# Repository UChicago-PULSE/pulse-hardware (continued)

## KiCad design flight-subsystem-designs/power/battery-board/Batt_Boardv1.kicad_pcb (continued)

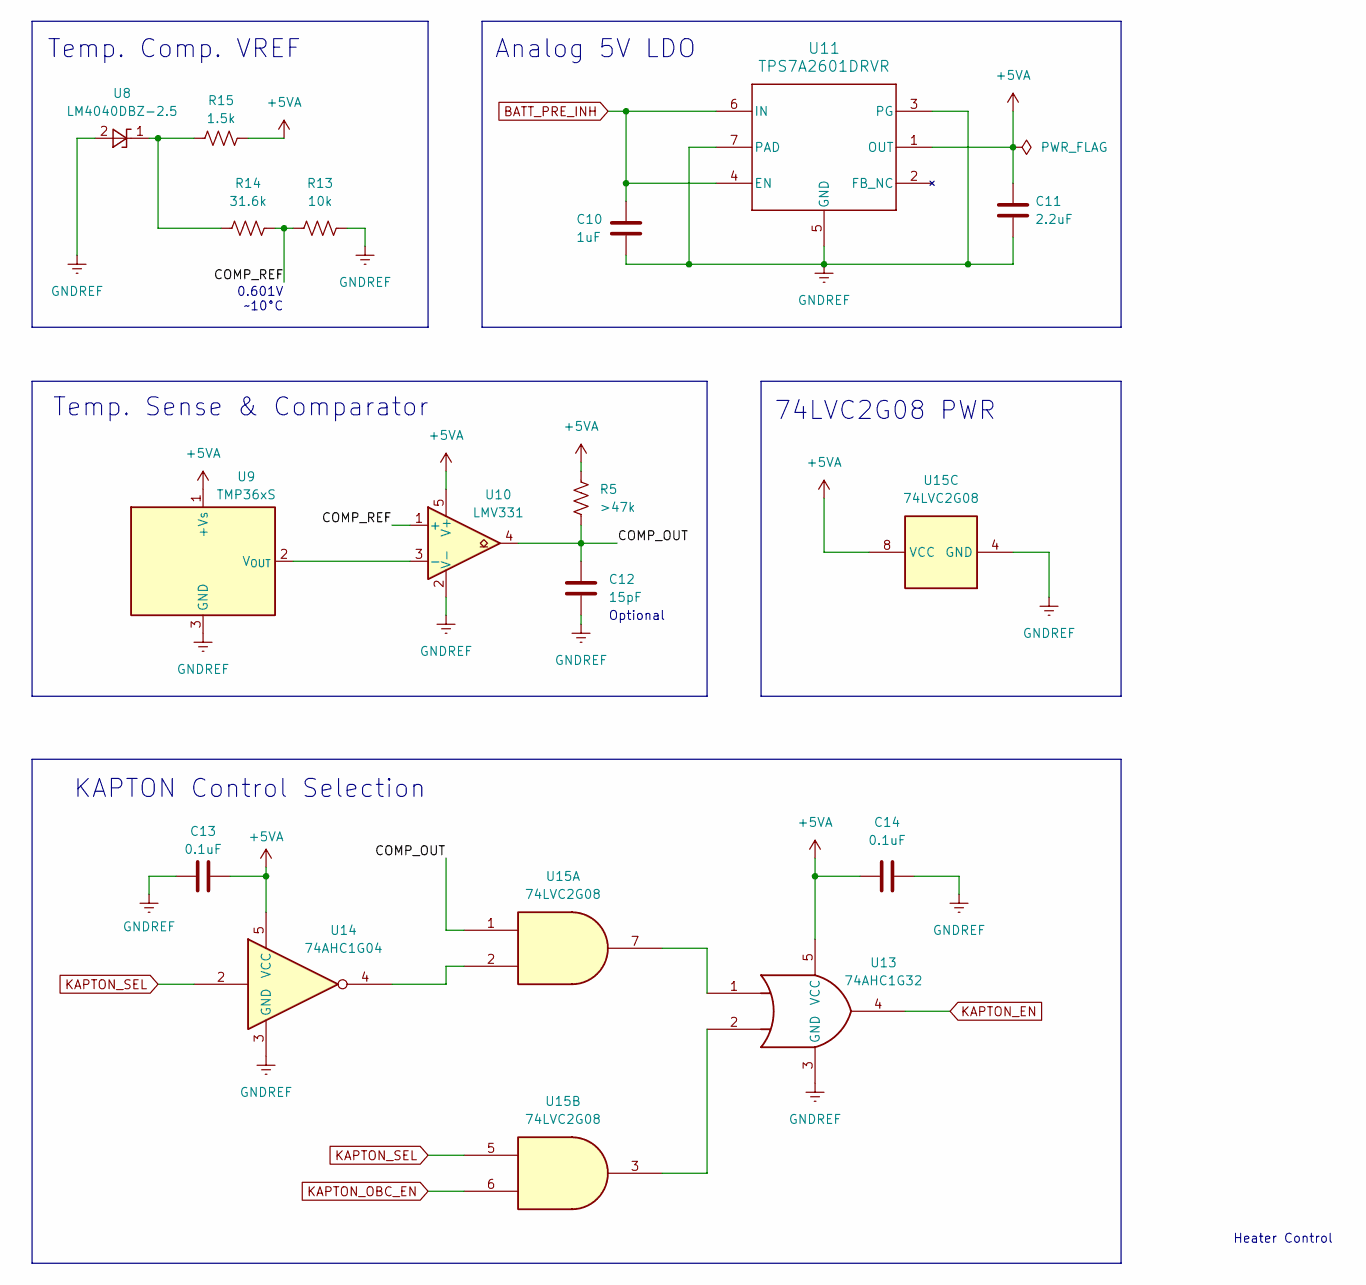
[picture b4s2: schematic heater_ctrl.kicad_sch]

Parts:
C10: 1uF; C_0805_2012Metric
C11: 2.2uF; C_0805_2012Metric
C12: 15pF; C_0805_2012Metric
C13, C14: 0.1uF; C_0805_2012Metric
R5: >47k; R_0805_2012Metric
R13: 10k; R_0805_2012Metric
R14: 31.6k; R_0805_2012Metric
R15: 1.5k; R_0805_2012Metric
U8: LM4040DBZ-2.5; SOT-23
U9: TMP36xS; TO-92_Inline
U10: LMV331; SOT-23-5
U11: TPS7A2601DRVR; DRV0006A_NV
U13: 74AHC1G32; SOT-23-5
U14: 74AHC1G04; SOT-23-5
U15: 74LVC2G08; VSSOP-8_2.3x2mm_P0.5mm

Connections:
+5VA: C11.1, C13.2, C14.1, R5.1, R15.2, U9.1 (+Vs), U10.5 (V+), U11.1 (OUT), U13.5 (VCC), U14.5 (VCC), U15.8 (VCC); also elsewhere on the board
/Heater Control/COMP_OUT: C12.1, R5.2, U10.4, U15.1
/Heater Control/COMP_REF: R13.1, R14.2, U10.1 (+)
BATT_PRE_INH: C10.1, U11.4 (EN), U11.6 (IN); also elsewhere on the board
GNDREF: C10.2, C11.2, C12.2, C13.1, C14.2, R13.2, U8.2 (A), U9.3 (GND), U10.2 (V-), U11.3 (PG), U11.5 (GND), U11.7 (PAD), U13.3 (GND), U14.3 (GND), U15.4 (GND); also elsewhere on the board
KAPTON_EN: U13.4; also elsewhere on the board
KAPTON_OBC_EN: U15.6; also elsewhere on the board
KAPTON_SEL: U14.2, U15.5; also elsewhere on the board
unnamed: R14.1, R15.1, U8.1 (K)
unnamed: U9.2 (V_{OUT}), U10.3 (-)
unnamed: U13.1, U15.7
unnamed: U13.2, U15.3
unnamed: U14.4, U15.2

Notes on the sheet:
Temp. Comp. VREF
Optional
Temp. Sense & Comparator
KAPTON Control Selection
Analog 5V LDO
Heater Control
0.601V ~10°C
74LVC2G08 PWR

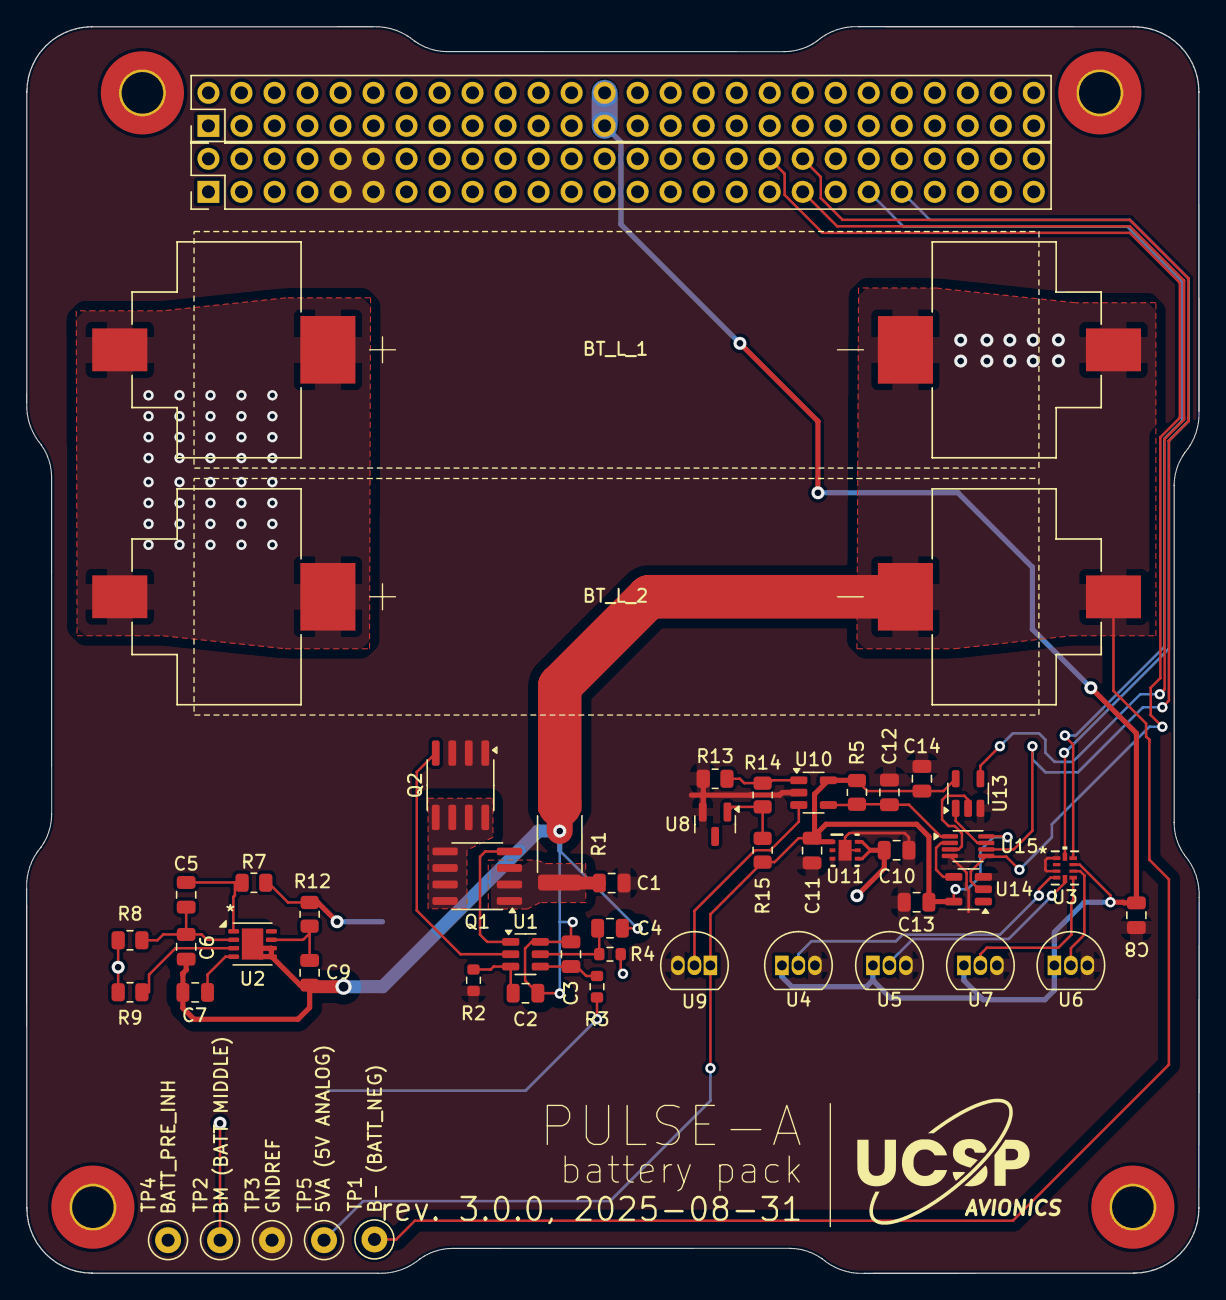
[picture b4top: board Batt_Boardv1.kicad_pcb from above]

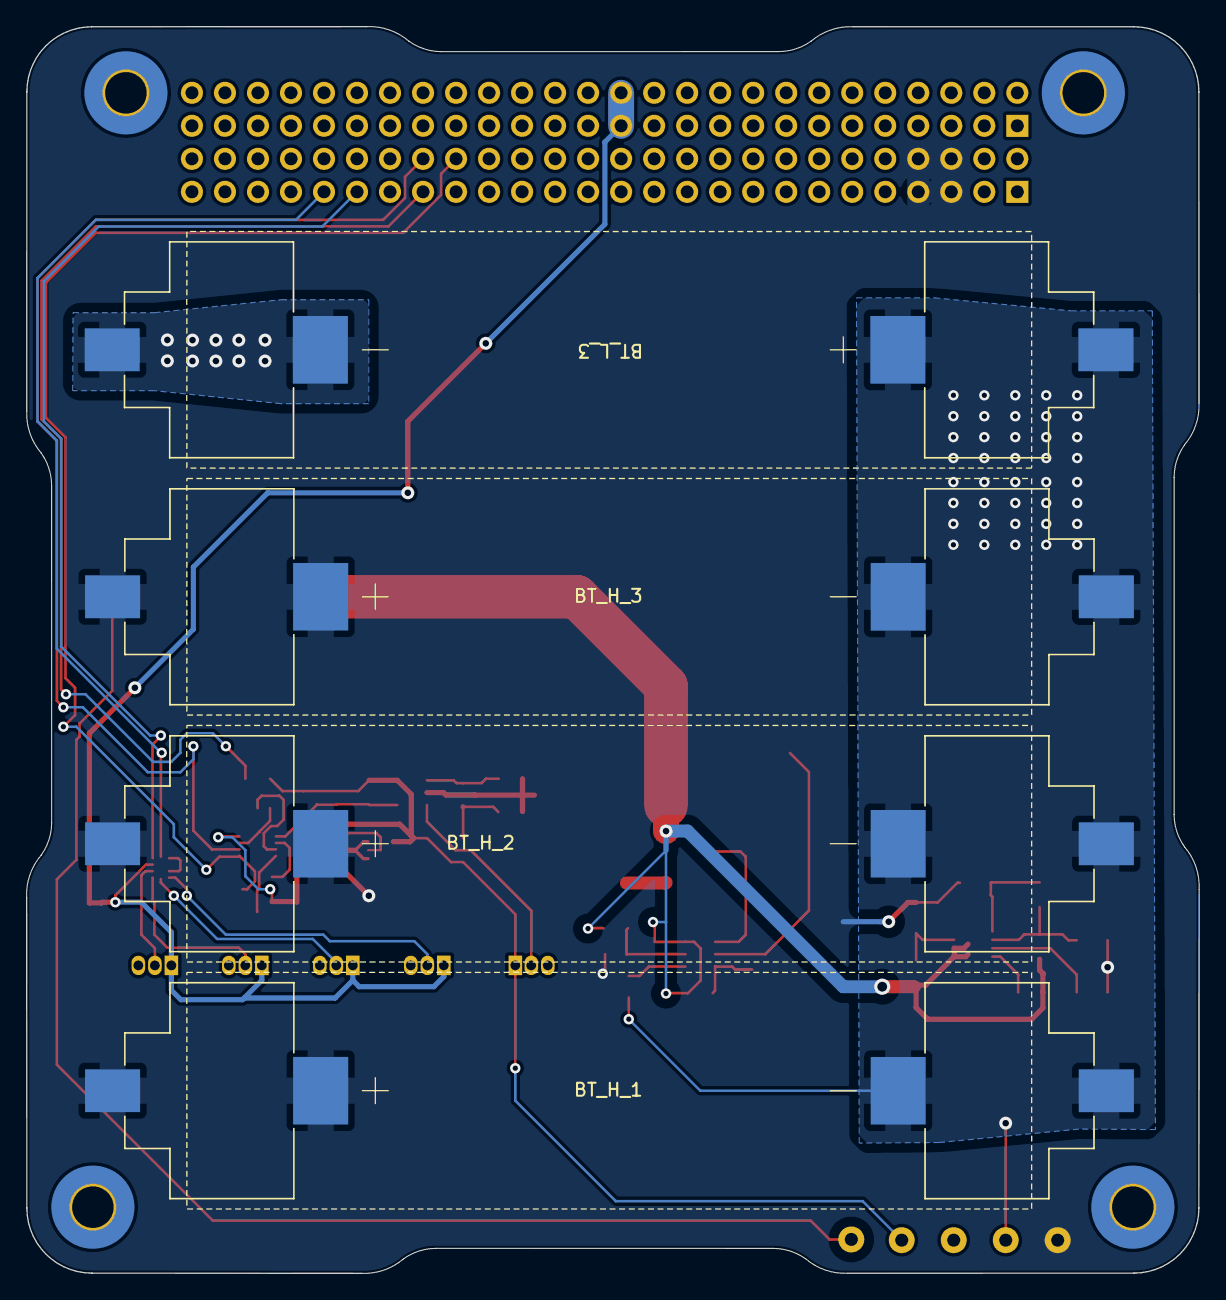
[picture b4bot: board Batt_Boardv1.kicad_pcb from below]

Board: 2 copper layers, 90.2 x 95.9 mm, 59 parts (4 on the bottom side), 34 nets.

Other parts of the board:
TP5: TestPoint; TestPoint_Loop_D1.80mm_Drill1.0mm_Beaded

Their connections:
+5VA: TP5.1; also elsewhere on the board

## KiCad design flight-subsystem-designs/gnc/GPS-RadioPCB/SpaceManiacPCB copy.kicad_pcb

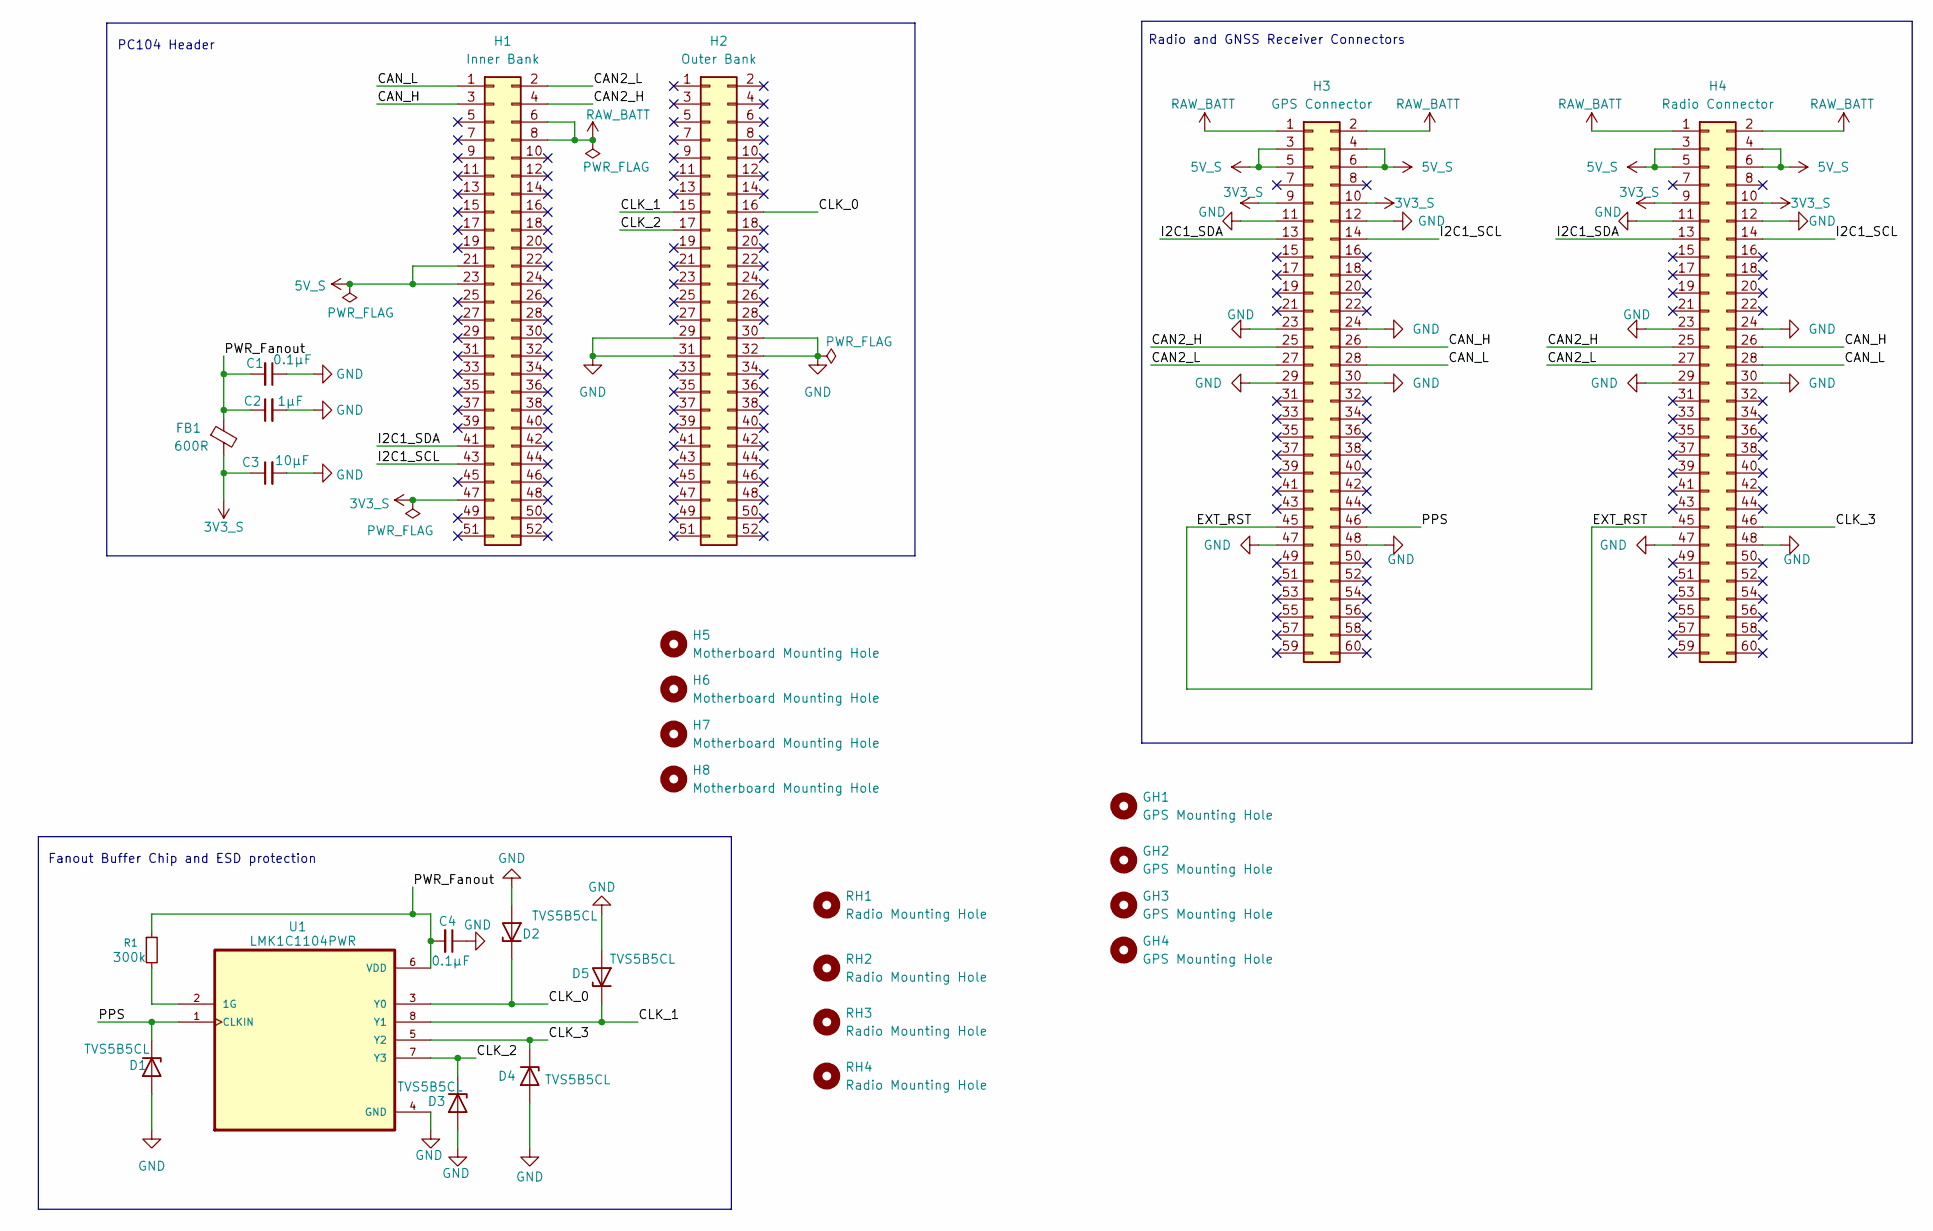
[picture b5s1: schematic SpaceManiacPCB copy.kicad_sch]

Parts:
C1, C4: 0.1μF; C_0402_1005Metric
C2: 1μF; C_0402_1005Metric
C3: 10μF; C_0402_1005Metric
D1, D2, D3, D4, D5: TVS5B5CL; Nexperia_DSN1608-2_1.6x0.8mm
FB1: 600R; L_0603_1608Metric
GH1, GH2, GH3, GH4: GPS Mounting Hole; MountingHole_2.5mm_Pad_TopBottom
H1: Inner Bank; PinHeader_2x26_P2.54mm_Vertical
H2: Outer Bank; PinHeader_2x26_P2.54mm_Vertical
H3: GPS Connector; CON_MolexSlimStack_54363-0689
H4: Radio Connector; CON_MolexSlimStack_54363-0689
H5, H6, H7, H8: Motherboard Mounting Hole; MountingHole_3.2mm_M3_Pad_TopBottom
R1: 300k; R_0603_1608Metric
RH1, RH2, RH3, RH4: Radio Mounting Hole; MountingHole_2.5mm_Pad_TopBottom
U1: LMK1C1104PWR; SOP65P640X120-8N; DigiKey_Part_Number 296-LMK1C1104PWRTR-ND

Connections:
3V3_S: C3.1, FB1.2, H1.47, H3.9, H3.10, H4.9, H4.10
5V_S: H1.21, H1.23, H3.3, H3.4, H3.5, H3.6, H4.3, H4.4, H4.5, H4.6
/CAN2_H: H1.4, H3.25, H4.25
/CAN2_L: H1.2, H3.27, H4.27
/CAN_H: H1.3, H3.26, H4.26
/CAN_L: H1.1, H3.28, H4.28
/CLK_0: D2.1 (K), H2.16, U1.3 (Y0)
/CLK_1: D5.1 (K), H2.15, U1.8 (Y1)
/CLK_2: D3.1 (K), H2.17, U1.7 (Y3)
/CLK_3: D4.1 (K), H4.46, U1.5 (Y2)
/EXT_RST: H3.45, H4.45
/I2C1_SCL: H1.43, H3.14, H4.14
/I2C1_SDA: H1.41, H3.13, H4.13
/PPS: D1.1 (K), H3.46, U1.1 (CLKIN)
/PWR_Fanout: C1.2, C2.1, C4.2, FB1.1, R1.1, U1.6 (VDD)
GND: C1.1, C2.2, C3.2, C4.1, D1.2 (A), D2.2 (A), D3.2 (A), D4.2 (A), D5.2 (A), H2.29, H2.30, H2.31, H2.32, H3.11, H3.12, H3.23, H3.24, H3.29, H3.30, H3.47, H3.48, H4.11, H4.12, H4.23, H4.24, H4.29, H4.30, H4.47, H4.48, U1.4 (GND)
unnamed: R1.2, U1.2 (1G)
RAW_BATT: H1.6, H1.8, H3.1, H3.2, H4.1, H4.2

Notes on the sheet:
PC104 Header
Fanout Buffer Chip and ESD protection
Radio and GNSS Receiver Connectors

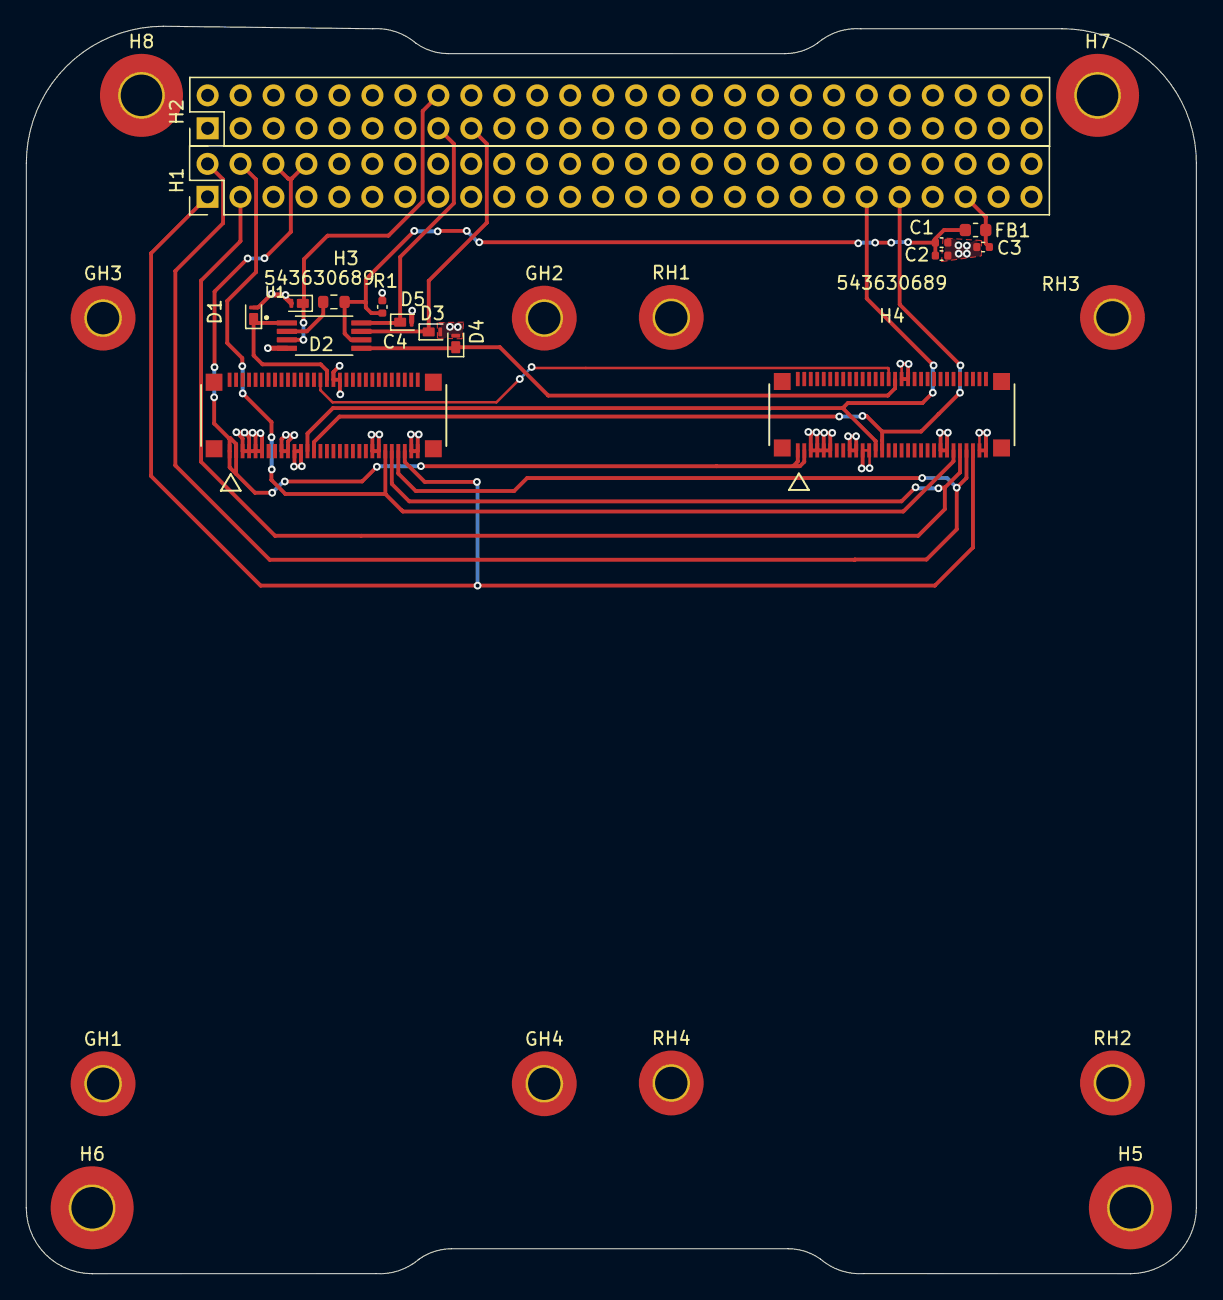
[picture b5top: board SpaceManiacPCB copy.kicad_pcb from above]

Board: 4 copper layers, 90.2 x 96.1 mm, 28 parts (0 on the bottom side), 18 nets.

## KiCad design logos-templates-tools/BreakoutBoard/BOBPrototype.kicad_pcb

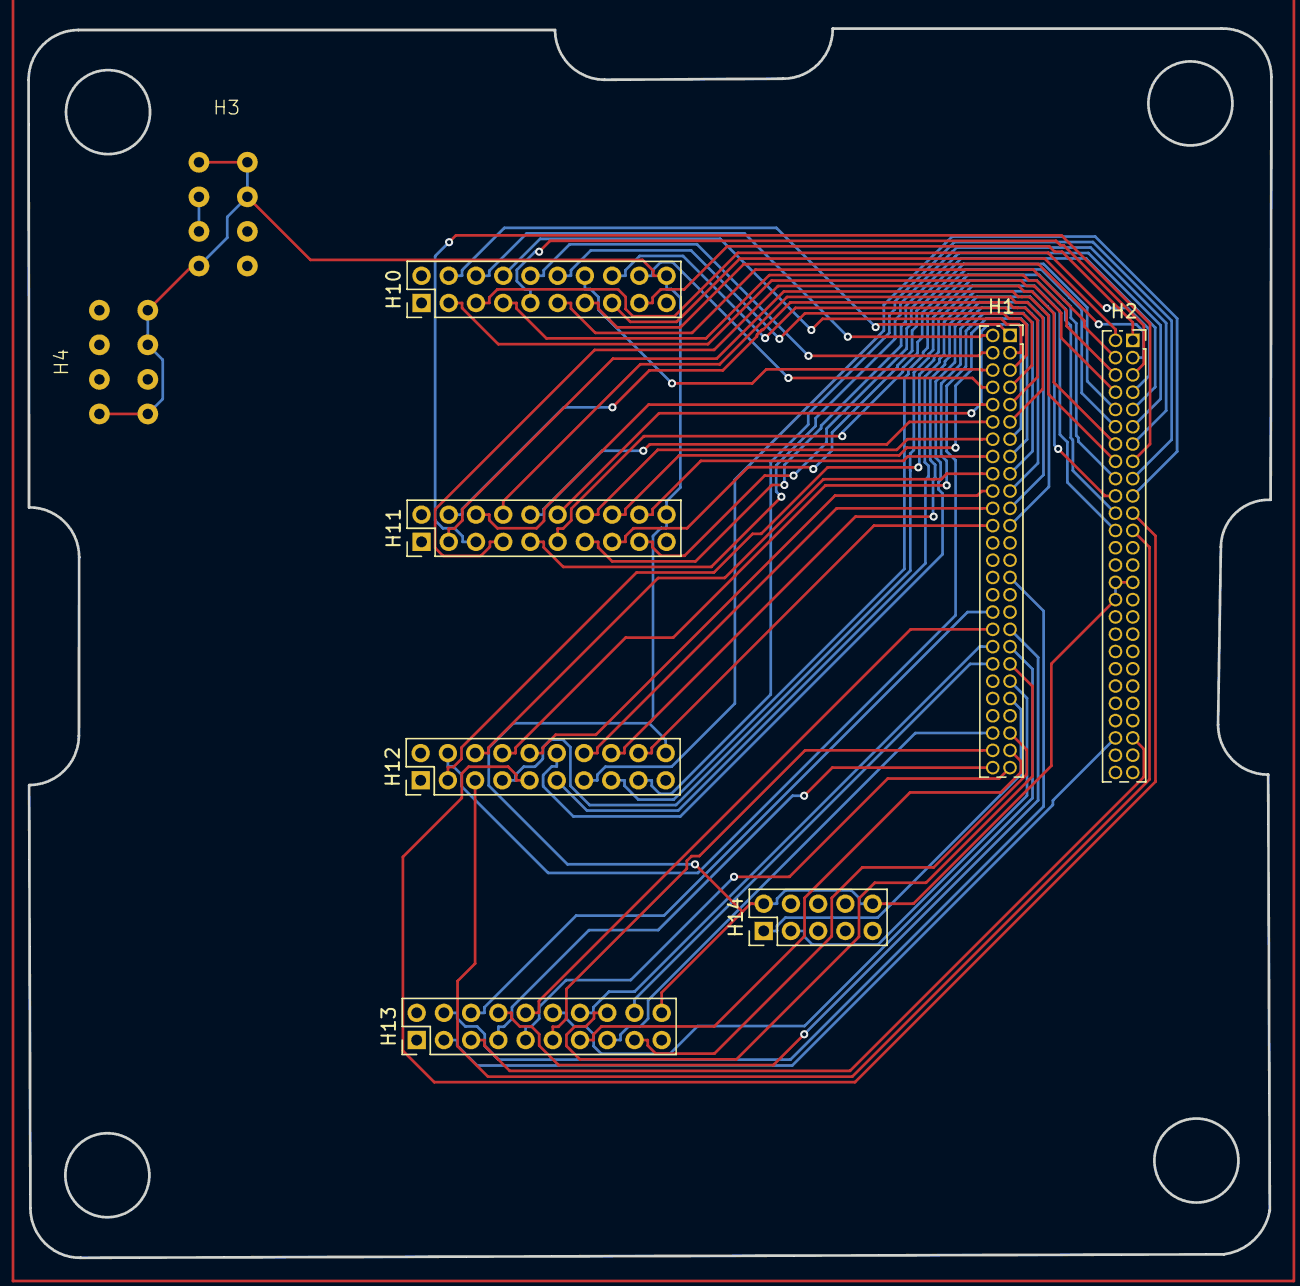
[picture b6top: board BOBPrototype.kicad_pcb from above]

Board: 2 copper layers, 91.3 x 90.3 mm, 9 parts (0 on the bottom side), 68 nets.

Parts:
H1, H2: PinSocket_2x26_P1.27mm_Vertical
H3: 5V32; H3
H4: 5V20; H4
H10, H11, H12, H13: Conn_02x10_Odd_Even; PinHeader_2x10_P2.00mm_Vertical
H14: Conn_02x05_Odd_Even; PinHeader_2x05_P2.00mm_Vertical

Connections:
Battery: H3.6 (+5V), H3.58 (+5V)
GND: H2.29 (GND), H2.30 (GND), H2.32 (GND), H3.2 (GND), H3.62 (GND), H3.63 (GND), H3.64 (GND), H4.1 (GND), H4.2 (GND), H4.37 (GND), H4.39 (GND), H10.20, H11.20, H12.20, H13.20, H14.2, H14.10
unnamed: H1.35 (-CTS_MHX), H13.8
unnamed: H1.37 (-DSR_MHX), H13.12
unnamed: H1.38 (-DTR_MHX), H13.14
unnamed: H1.29 (-RESET), H13.4
unnamed: H1.34 (-RST_MHX), H13.6
unnamed: H1.36 (-RTS_MHX), H13.10
unnamed: H1.24 (P3.0), H12.18
unnamed: H1.23 (P3.1), H12.16
unnamed: H1.22 (P3.2), H12.14
unnamed: H1.21 (P3.3), H12.12
unnamed: H1.20 (P3.4), H12.10
unnamed: H1.19 (P3.5), H12.8
unnamed: H1.18 (P3.6), H12.6
unnamed: H1.17 (P3.7), H12.4
unnamed: H1.16 (P4.0), H11.18
unnamed: H1.15 (P4.1), H11.16
unnamed: H1.14 (P4.2), H11.14
unnamed: H1.13 (P4.3), H11.12
unnamed: H1.12 (P4.4), H11.10
unnamed: H1.11 (P4.5), H11.8
unnamed: H1.10 (P4.6), H11.6
unnamed: H1.9 (P4.7), H11.4
unnamed: H1.8 (P5.0), H10.18
unnamed: H1.7 (P5.1), H10.16
unnamed: H1.6 (P5.2), H10.14
unnamed: H1.5 (P5.3), H10.12
unnamed: H1.4 (P5.4), H10.10
unnamed: H1.3 (P5.5), H10.8
unnamed: H1.2 (P5.6), H10.6
unnamed: H1.1 (P5.7), H10.4
unnamed: H1.40 (RXD_MHX), H13.18
unnamed: H1.43 (SCL_SYS), H14.1
unnamed: H1.41 (SDA_SYS), H14.3
unnamed: H1.39 (TXD_MHX), H13.16
unnamed: H1.47 (USER0), H13.17
unnamed: H1.48 (USER1), H13.15
unnamed: H1.49 (USER2), H13.13
unnamed: H1.50 (USER3), H13.11
unnamed: H1.51 (USER4), H13.9
unnamed: H1.52 (USER5), H13.7
unnamed: H2.8 (P6.0), H10.3
unnamed: H2.7 (P6.1), H10.5
unnamed: H2.6 (P6.2), H10.7
unnamed: H2.5 (P6.3), H10.9
unnamed: H2.4 (P6.4), H10.11
unnamed: H2.3 (P6.5), H10.13
unnamed: H2.2 (P6.6), H10.15
unnamed: H2.1 (P6.7), H10.17
unnamed: H2.16 (P1.0), H11.3
unnamed: H2.15 (P1.1), H11.5
unnamed: H2.14 (P1.2), H11.7
unnamed: H2.13 (P1.3), H11.9
unnamed: H2.12 (P1.4), H11.11
unnamed: H2.11 (P1.5), H11.13
unnamed: H2.10 (P1.6), H11.15
unnamed: H2.9 (P1.7), H11.17
unnamed: H2.24 (P2.0), H12.3
unnamed: H2.23 (P2.1), H12.5
unnamed: H2.22 (P2.2), H12.7
unnamed: H2.21 (P2.3), H12.9
unnamed: H2.20 (P2.4), H12.11
unnamed: H2.19 (P2.5), H12.13
unnamed: H2.18 (P2.6), H12.15
unnamed: H2.17 (P2.7), H12.17
unnamed: H2.48 (USER7), H13.3
unnamed: H2.47 (USER6), H13.5

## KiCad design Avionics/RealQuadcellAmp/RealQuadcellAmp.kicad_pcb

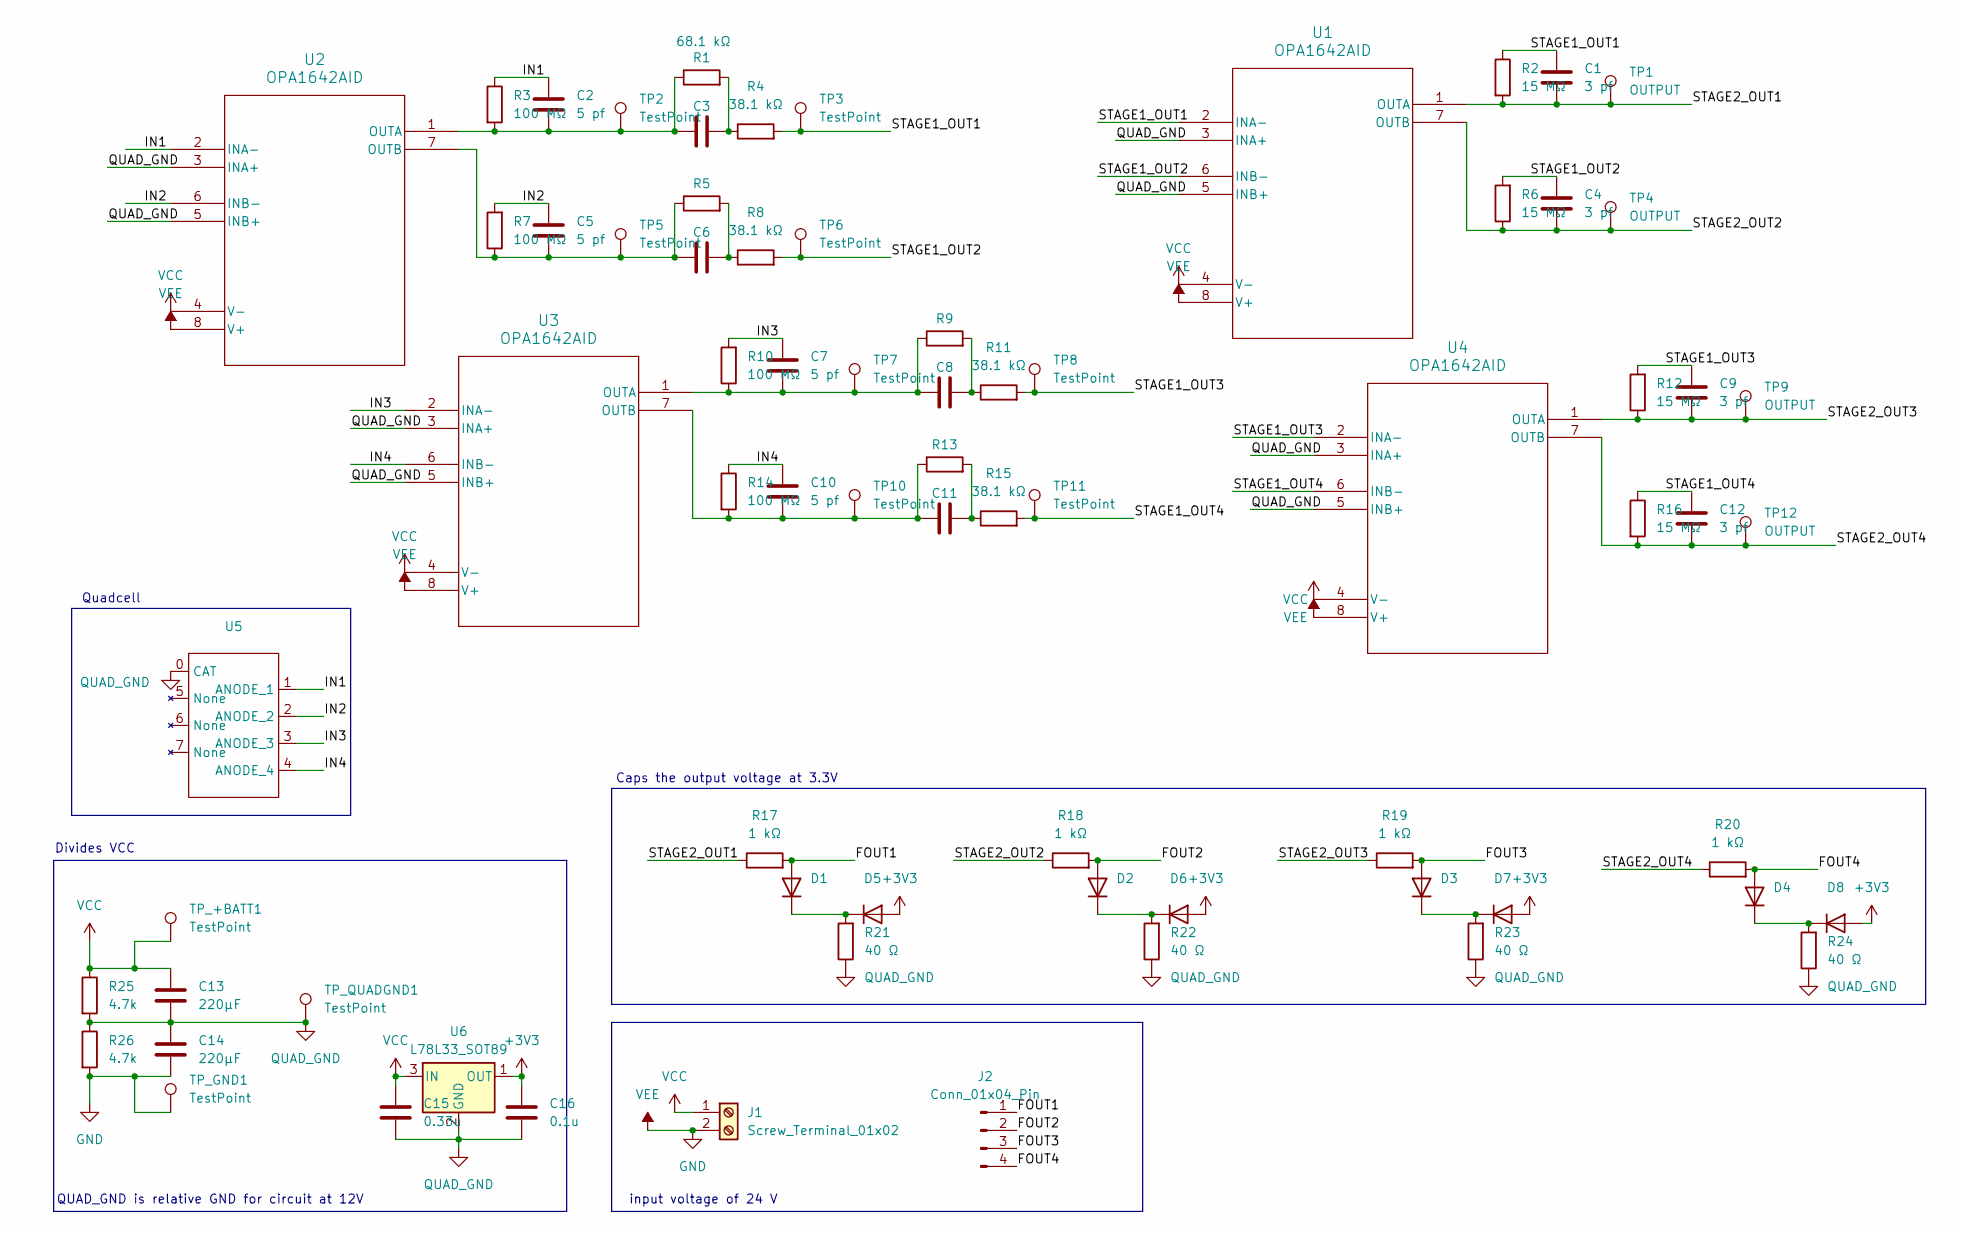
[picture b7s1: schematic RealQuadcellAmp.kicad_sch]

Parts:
C1, C4, C9, C12: 3 pf; C_0805_2012Metric_Pad1.18x1.45mm_HandSolder
C2, C5, C7, C10: 5 pf; C_0805_2012Metric_Pad1.18x1.45mm_HandSolder
C3, C6, C8, C11: 330 pf; C_0805_2012Metric_Pad1.18x1.45mm_HandSolder
C13, C14: 220µF; C_0805_2012Metric_Pad1.18x1.45mm_HandSolder
C15: 0.33u; C_0805_2012Metric_Pad1.18x1.45mm_HandSolder
C16: 0.1u; C_0805_2012Metric_Pad1.18x1.45mm_HandSolder
D1, D2, D3, D4, D5, D6, D7, D8: D_0805_2012Metric_Pad1.15x1.40mm_HandSolder
J1: Screw_Terminal_01x02; TerminalBlock_bornier-2_P5.08mm
J2: Conn_01x04_Pin; PinHeader_1x04_P2.54mm_Vertical
R1, R5, R9, R13: 68.1 kΩ; R_0805_2012Metric_Pad1.20x1.40mm_HandSolder
R2, R6, R12, R16: 15 MΩ; R_0805_2012Metric_Pad1.20x1.40mm_HandSolder
R3, R7, R10, R14: 100 MΩ; R_0805_2012Metric_Pad1.20x1.40mm_HandSolder
R4, R8, R11, R15: 38.1 kΩ; R_0805_2012Metric_Pad1.20x1.40mm_HandSolder
R17, R18, R19, R20: 1 kΩ; R_0805_2012Metric_Pad1.20x1.40mm_HandSolder
R21, R22, R23, R24: 40 Ω; R_0805_2012Metric_Pad1.20x1.40mm_HandSolder
R25, R26: 4.7k; R_0805_2012Metric_Pad1.20x1.40mm_HandSolder
TP1, TP4, TP9, TP12: OUTPUT; TestPoint_Loop_D2.50mm_Drill1.0mm
TP2, TP3, TP5, TP6, TP7, TP8, TP10, TP11: TestPoint; TestPoint_Pad_2.0x2.0mm
TP_+BATT1: TestPoint; TestPoint_THTPad_1.0x1.0mm_Drill0.5mm
TP_GND1: TestPoint; TestPoint_THTPad_1.0x1.0mm_Drill0.5mm
TP_QUADGND1: TestPoint; TestPoint_THTPad_1.0x1.0mm_Drill0.5mm
U1, U2, U3, U4: OPA1642AID; D8
U5: InGaAS-Q1000
U6: L78L33_SOT89; SOT-89-3

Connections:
+3V3: C16.1, D5.2 (A), D6.2 (A), D7.2 (A), D8.2 (A), U6.1 (OUT)
/FOUT1: D1.2 (A), J2.1, R17.2
/FOUT2: D2.2 (A), J2.2, R18.2
/FOUT3: D3.2 (A), J2.3, R19.2
/FOUT4: D4.2 (A), J2.4, R20.2
/IN1: C2.1, R3.1, U2.2 (INA-), U5.1 (ANODE_1)
/IN2: C5.1, R7.2, U2.6 (INB-), U5.2 (ANODE_2)
/IN3: C7.1, R10.2, U3.2 (INA-), U5.3 (ANODE_3)
/IN4: C10.1, R14.1, U3.6 (INB-), U5.4 (ANODE_4)
/STAGE1_OUT1: C1.1, R2.1, R4.2, TP3.1, U1.2 (INA-)
/STAGE1_OUT2: C4.1, R6.2, R8.2, TP6.1, U1.6 (INB-)
/STAGE1_OUT3: C9.1, R11.2, R12.2, TP8.1, U4.2 (INA-)
/STAGE1_OUT4: C12.1, R15.2, R16.1, TP11.1, U4.6 (INB-)
/STAGE2_OUT1: C1.2, R2.2, R17.1, TP1.1, U1.1 (OUTA)
/STAGE2_OUT2: C4.2, R6.1, R18.1, TP4.1, U1.7 (OUTB)
/STAGE2_OUT3: C9.2, R12.1, R19.1, TP9.1, U4.1 (OUTA)
/STAGE2_OUT4: C12.2, R16.2, R20.1, TP12.1, U4.7 (OUTB)
GND: C14.2, J1.2, R26.2, TP_GND1.1, U1.8 (V+), U2.8 (V+), U3.8 (V+), U4.8 (V+)
unnamed: C3.2, R1.2, R4.1
unnamed: C6.2, R5.2, R8.1
unnamed: C8.2, R9.2, R11.1
unnamed: C11.2, R13.2, R15.1
unnamed: D1.1 (K), D5.1 (K), R21.2
unnamed: D2.1 (K), D6.1 (K), R22.2
unnamed: D3.1 (K), D7.1 (K), R23.2
unnamed: D4.1 (K), D8.1 (K), R24.2
unnamed: C2.2, C3.1, R1.1, R3.2, TP2.1, U2.1 (OUTA)
unnamed: C5.2, C6.1, R5.1, R7.1, TP5.1, U2.7 (OUTB)
unnamed: C7.2, C8.1, R9.1, R10.1, TP7.1, U3.1 (OUTA)
unnamed: C10.2, C11.1, R13.1, R14.2, TP10.1, U3.7 (OUTB)
QUAD_GND: C13.2, C14.1, C15.2, C16.2, R21.1, R22.1, R23.1, R24.1, R25.2, R26.1, TP_QUADGND1.1, U1.3 (INA+), U1.5 (INB+), U2.3 (INA+), U2.5 (INB+), U3.3 (INA+), U3.5 (INB+), U4.3 (INA+), U4.5 (INB+), U5.0 (CAT), U6.2 (GND)
VCC: C13.1, C15.1, J1.1, R25.1, TP_+BATT1.1, U1.4 (V-), U2.4 (V-), U3.4 (V-), U4.4 (V-), U6.3 (IN)

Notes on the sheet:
Quadcell
Divides VCC
QUAD_GND is relative GND for circuit at 12V
input voltage of 24 V
Caps the output voltage at 3.3V

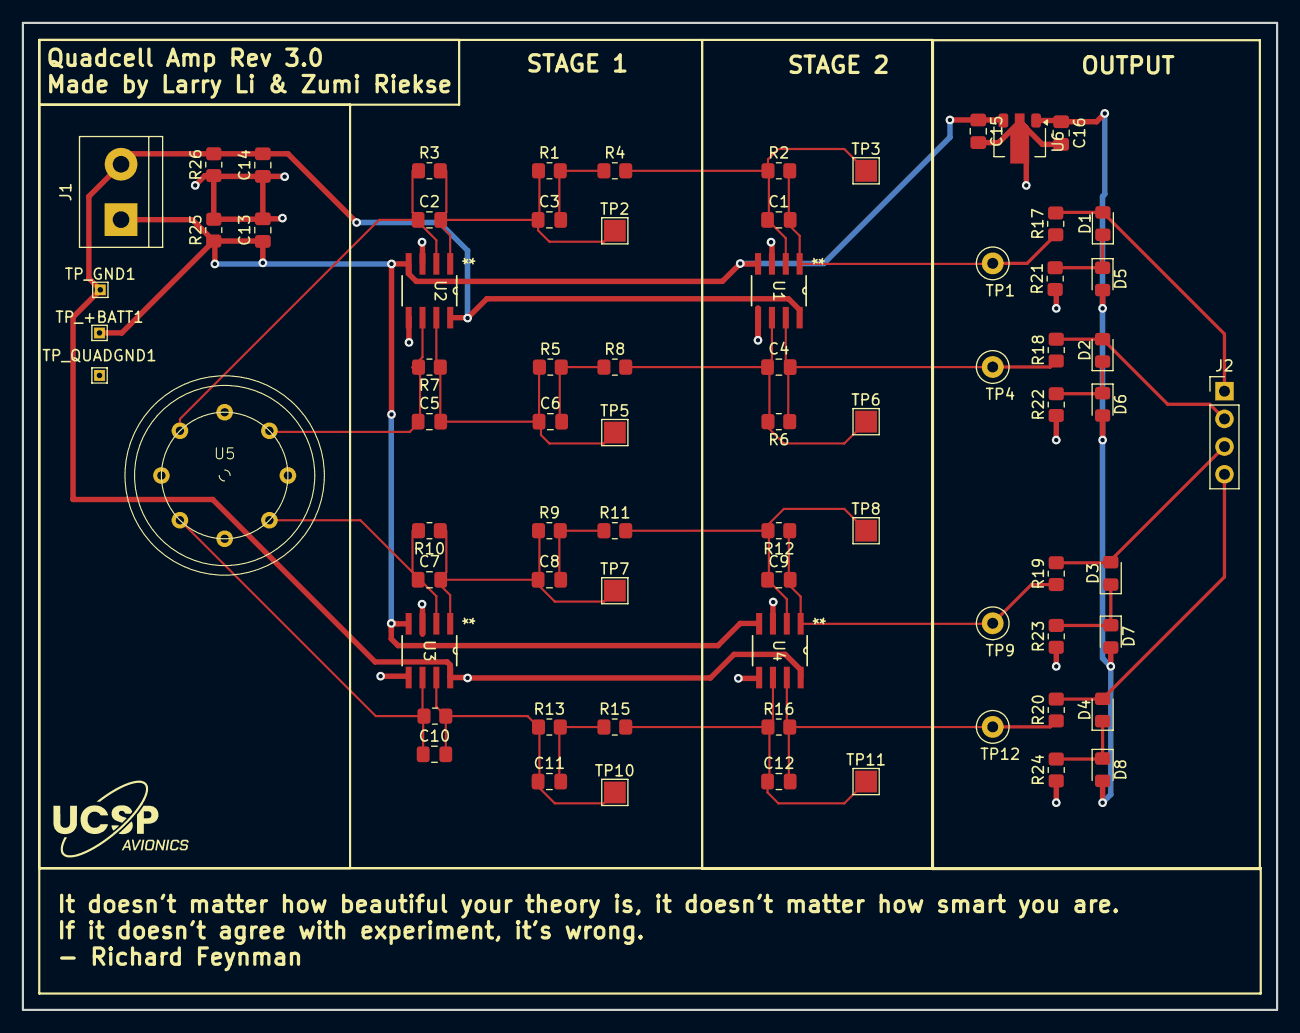
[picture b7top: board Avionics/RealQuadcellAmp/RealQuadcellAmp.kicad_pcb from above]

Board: 2 copper layers, 115.0 x 90.5 mm, 73 parts (0 on the bottom side), 32 nets.

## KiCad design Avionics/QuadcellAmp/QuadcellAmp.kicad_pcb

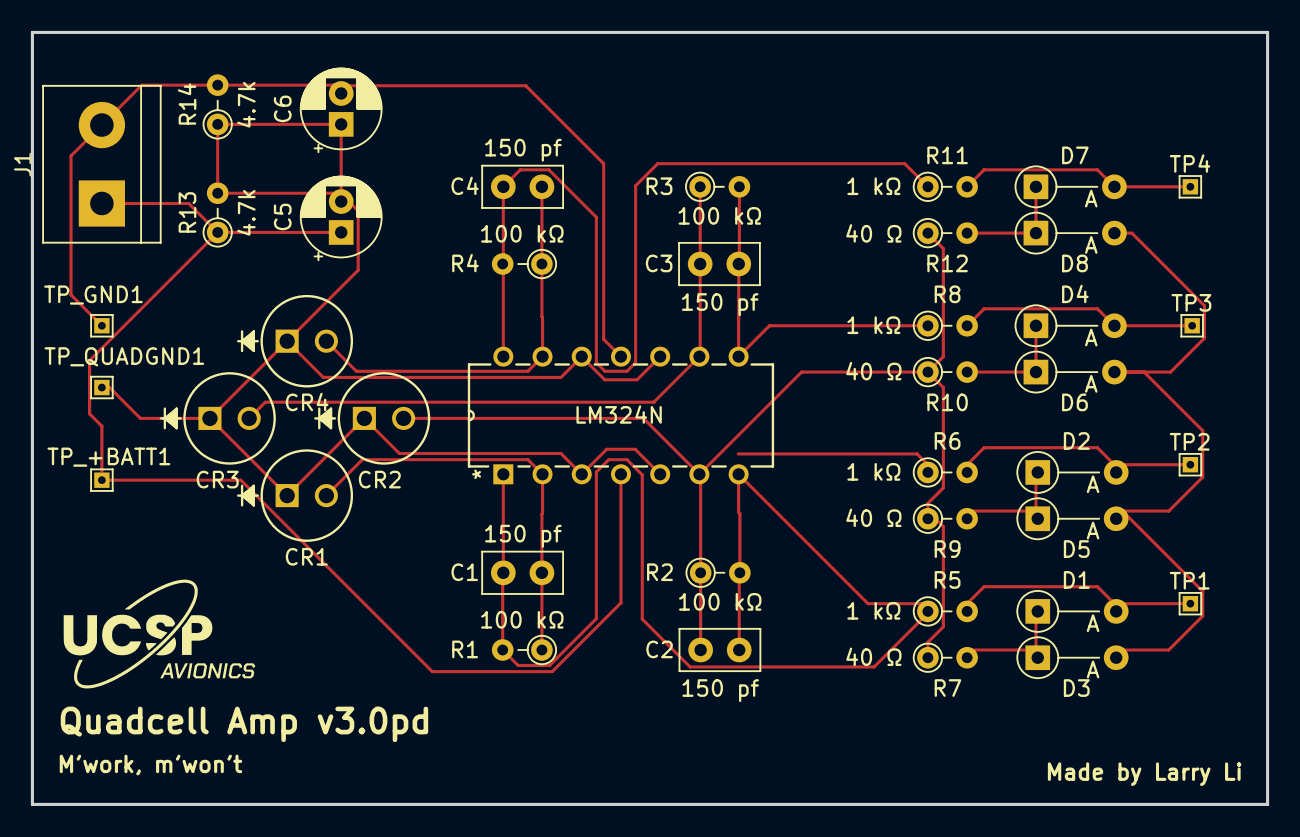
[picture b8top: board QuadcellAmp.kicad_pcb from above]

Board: 2 copper layers, 80.0 x 50.0 mm, 41 parts (0 on the bottom side), 20 nets.

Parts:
C1, C2, C3, C4: 150 pf; C_Disc_D5.0mm_W2.5mm_P2.50mm
C5, C6: 220µF; CP_Radial_D5.0mm_P2.00mm
CR1, CR2, CR3, CR4: PDB-C142; PDB-C142_ADP
D1, D2, D3, D4, D5, D6, D7, D8: D_DO-35_SOD27_P5.08mm_Vertical_AnodeUp
J1: Screw_Terminal_01x02; TerminalBlock_bornier-2_P5.08mm
R1, R2, R3, R4: 100 kΩ; R_Axial_DIN0204_L3.6mm_D1.6mm_P2.54mm_Vertical
R5, R6, R8, R11: 1 kΩ; R_Axial_DIN0204_L3.6mm_D1.6mm_P2.54mm_Vertical
R7, R9, R10, R12: 40 Ω; R_Axial_DIN0204_L3.6mm_D1.6mm_P2.54mm_Vertical
R13, R14: 4.7k; R_Axial_DIN0204_L3.6mm_D1.6mm_P2.54mm_Vertical
TP1, TP2, TP3, TP4: TestPoint; TestPoint_THTPad_1.0x1.0mm_Drill0.5mm
TP_+BATT1: TestPoint; TestPoint_THTPad_1.0x1.0mm_Drill0.5mm
TP_GND1: TestPoint; TestPoint_THTPad_1.0x1.0mm_Drill0.5mm
TP_QUADGND1: TestPoint; TestPoint_THTPad_1.0x1.0mm_Drill0.5mm
U2: LM324N; N14

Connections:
3V3: D3.2 (A), D5.2 (A), D6.2 (A), D8.2 (A)
+BATT: C5.1, J1.1, R13.1, TP_+BATT1.1, U2.4 (V+)
/Anode_A: C1.1, CR1.2, R1.1, U2.2 (-)
/Anode_B: C2.1, CR2.2, R2.1, U2.6 (-)
/Anode_C: C3.1, CR3.2, R3.1, U2.9 (-)
/Anode_D: C4.1, CR4.2, R4.1, U2.13 (-)
GND: C6.2, J1.2, R14.2, TP_GND1.1, U2.11 (V-)
unnamed: C1.2, R1.2, R5.1, U2.1
unnamed: C2.2, R2.2, R6.1, U2.7
unnamed: C3.2, R3.2, R8.1, U2.8
unnamed: C4.2, R4.2, R11.1, U2.14
unnamed: D1.2 (A), R5.2, TP1.1
unnamed: D1.1 (K), D3.1 (K), R7.2
unnamed: D2.2 (A), R6.2, TP2.1
unnamed: D2.1 (K), D5.1 (K), R9.2
unnamed: D4.2 (A), R8.2, TP3.1
unnamed: D4.1 (K), D6.1 (K), R10.2
unnamed: D7.2 (A), R11.2, TP4.1
unnamed: D7.1 (K), D8.1 (K), R12.2
QUAD_GND: C5.2, C6.1, CR1.1, CR2.1, CR3.1, CR4.1, R7.1, R9.1, R10.1, R12.1, R13.2, R14.1, TP_QUADGND1.1, U2.3 (+), U2.5 (+), U2.10 (+), U2.12 (+)
